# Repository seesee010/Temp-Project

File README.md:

# Custom PCB

> [!IMPORTANT]
> You will only find the kicad here, as everything else is not finished,yet!

This is my project, fully made with KiCad.
The purpose is that it will show temp and hum on display (spi).

## Preview
View PDF: [PDF-Workflow](./docs/pdf/Temp-Project.pdf)

View Website: [Website](https://seesee010.github.io/Temp-Project/)

View PCB:

## License
GPL 2.0 - see License file for more Information.

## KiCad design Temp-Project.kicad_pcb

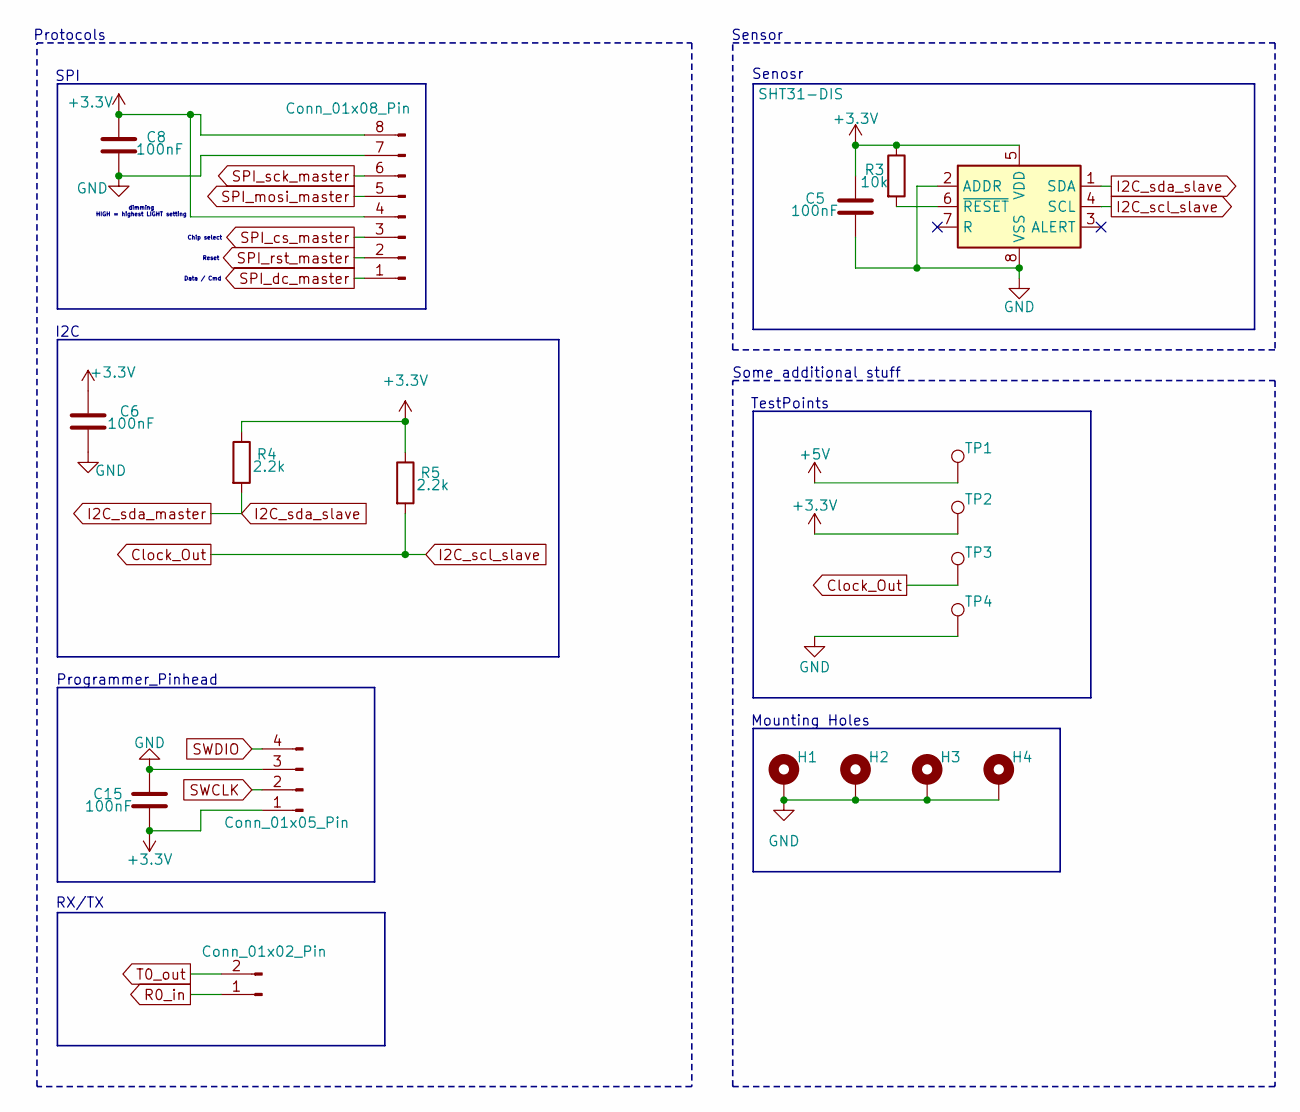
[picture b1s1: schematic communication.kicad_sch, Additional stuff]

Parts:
C5, C6, C8, C15: 100nF; C_0603_1608Metric
H1, H2, H3, H4: MountingHole_Pad; MountingHole_2.2mm_M2_DIN965_Pad
J2: Conn_01x05_Pin; PinHeader_1x05_P2.54mm_Vertical
J3: Conn_01x02_Pin; PinHeader_1x02_P2.54mm_Vertical
J4: Conn_01x08_Pin; PinHeader_1x08_P2.54mm_Vertical
R3: 10k; R_0402_1005Metric
R4, R5: 2.2k; R_0402_1005Metric
TP1, TP2, TP3, TP4: TestPoint; TestPoint_Pad_1.0x1.0mm
U3: SHT31-DIS; Texas_S-PWSON-N6-HDC2080

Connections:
+3.3V: C5.1, C6.1, C8.1, C15.2, J2.1, J4.4, J4.8, R3.1, R4.1, R5.1, TP2.1, U3.5 (VDD); also elsewhere on the board
+5V: TP1.1; also elsewhere on the board
Clock_Out: R5.2, TP3.1, U3.4 (SCL); also elsewhere on the board
GND: C5.2, C6.2, C8.2, C15.1, H1.1, H2.1, H3.1, H4.1, J2.3, J4.7, TP4.1, U3.2 (ADDR), U3.8 (VSS), U3.9 (VSS); also elsewhere on the board
I2C_sda_master: R4.2, U3.1 (SDA); also elsewhere on the board
unnamed: R3.2, U3.6 (~RESET)
R0_in: J3.1; also elsewhere on the board
SPI_cs_master: J4.3; also elsewhere on the board
SPI_dc_master: J4.1; also elsewhere on the board
SPI_mosi_master: J4.5; also elsewhere on the board
SPI_rst_master: J4.2; also elsewhere on the board
SPI_sck_master: J4.6; also elsewhere on the board
SWCLK: J2.2; also elsewhere on the board
SWDIO: J2.4; also elsewhere on the board
T0_out: J3.2; also elsewhere on the board

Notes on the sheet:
TestPoints
Programmer_Pinhead
Senosr
SPI
Reset
Some additional stuff
dimming HIGH = highest LIGHT setting
Mounting Holes
RX/TX
I2C
Data / Cmd
Protocols
Sensor
Chip select

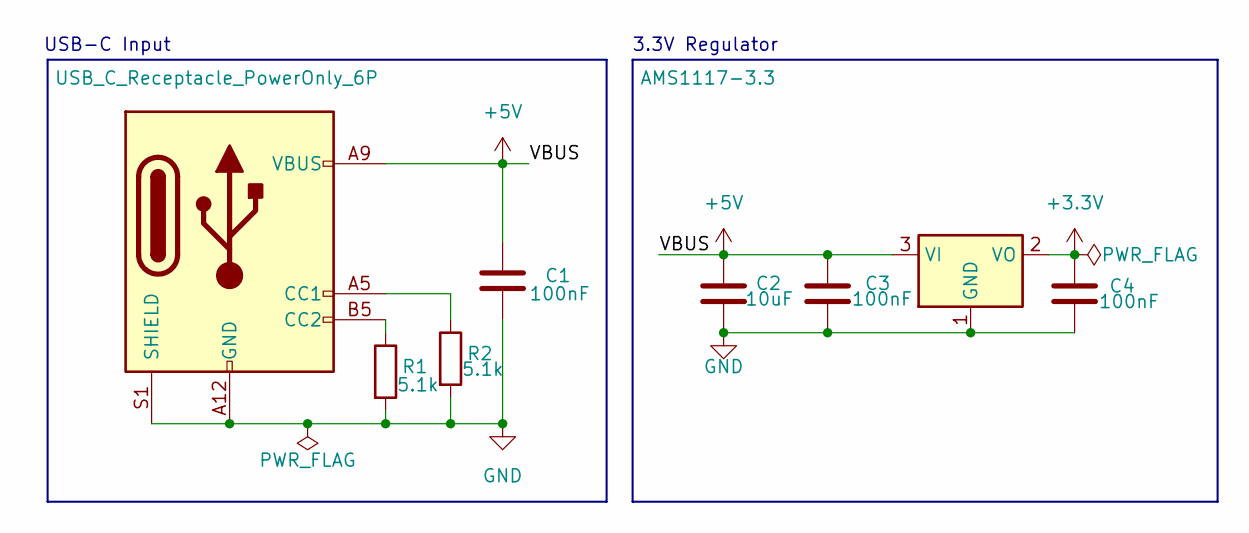
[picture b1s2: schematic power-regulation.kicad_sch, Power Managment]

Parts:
C1, C3, C4: 100nF; C_0603_1608Metric
C2: 10uF; C_0603_1608Metric
J1: USB_C_Receptacle_PowerOnly_6P; USB_C_Receptacle_GCT_USB4135-GF-A_6P_TopMnt_Horizontal
R1, R2: 5.1k; R_0402_1005Metric
U1: AMS1117-3.3; SOT-223-3_TabPin2

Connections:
+3.3V: C4.1, U1.2 (VO); also elsewhere on the board
+5V: C1.2, C2.1, C3.1, J1.A9 (VBUS), J1.B9 (VBUS), U1.3 (VI); also elsewhere on the board
GND: C1.1, C2.2, C3.2, C4.2, J1.A12 (GND), J1.B12 (GND), J1.S1 (SHIELD), R1.2, R2.2, U1.1 (GND); also elsewhere on the board
unnamed: J1.A5 (CC1), R2.1
unnamed: J1.B5 (CC2), R1.1

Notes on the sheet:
USB-C Input
3.3V Regulator

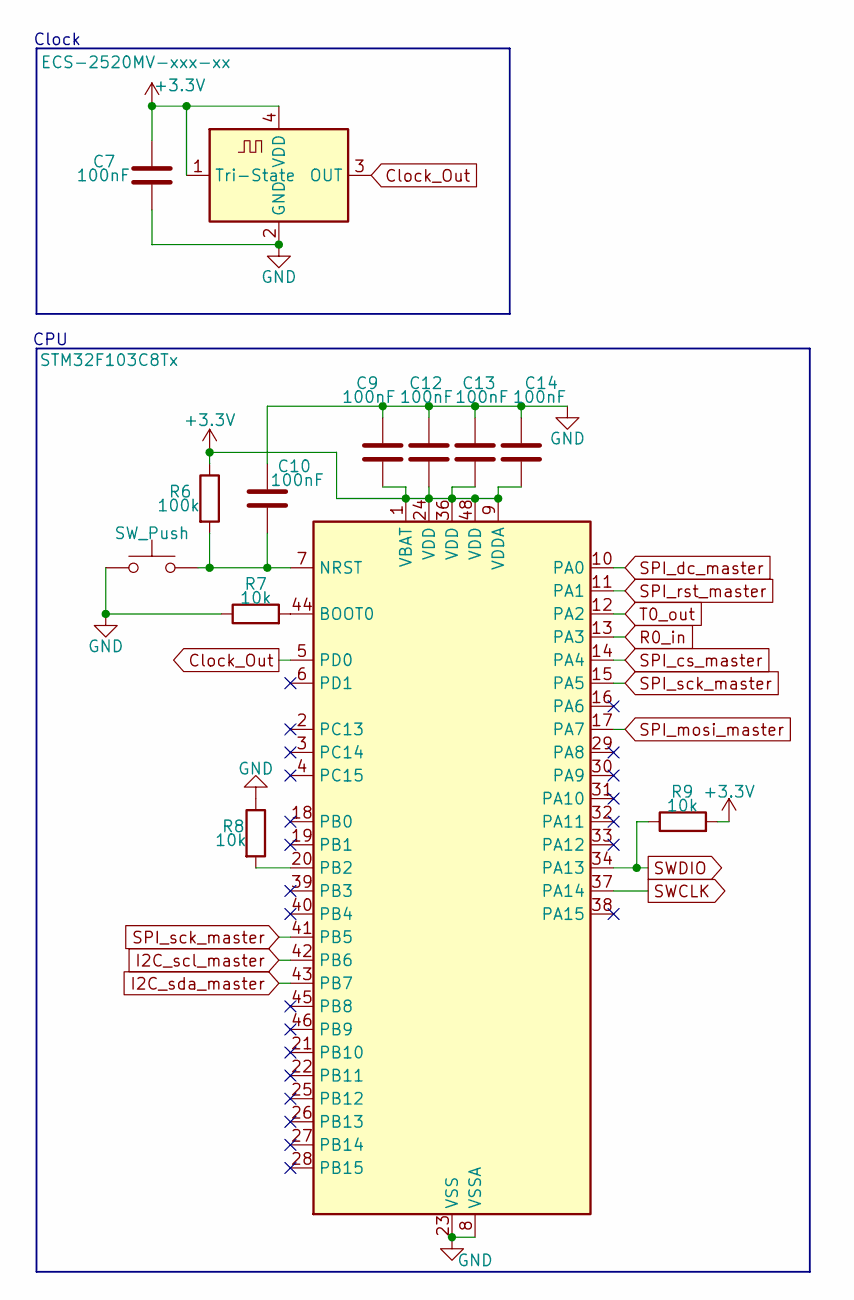
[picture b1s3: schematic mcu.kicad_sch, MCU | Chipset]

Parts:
C7, C9, C10, C12, C13, C14: 100nF; C_0603_1608Metric
R6: 100k; R_0402_1005Metric
R7, R8, R9: 10k; R_0402_1005Metric
SW1: SW_Push; SW_Push_1P1T_NO_CK_KMR2
U2: STM32F103C8Tx; LQFP-48_7x7mm_P0.5mm
Y1: ECS-2520MV-xxx-xx; Oscillator_SMD_EuroQuartz_XO53-4Pin_5.0x3.2mm

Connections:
+3.3V: C7.1, C9.2, C12.2, C13.2, C14.2, R6.1, R9.2, U2.1 (VBAT), U2.9 (VDDA), U2.24 (VDD), U2.36 (VDD), U2.48 (VDD), Y1.1 (Tri-State), Y1.4 (VDD); also elsewhere on the board
Clock_Out: U2.5 (PD0), Y1.3 (OUT); also elsewhere on the board
GND: C7.2, C9.1, C10.1, C12.1, C13.1, C14.1, R7.1, R8.1, SW1.1, U2.8 (VSSA), U2.23 (VSS), U2.35 (VSS), U2.47 (VSS), Y1.2 (GND); also elsewhere on the board
I2C_scl_master: U2.42 (PB6)
I2C_sda_master: U2.43 (PB7); also elsewhere on the board
unnamed: R7.2, U2.44 (BOOT0)
unnamed: C10.2, R6.2, SW1.2, U2.7 (NRST)
unnamed: R8.2, U2.20 (PB2)
R0_in: U2.13 (PA3); also elsewhere on the board
SPI_cs_master: U2.14 (PA4); also elsewhere on the board
SPI_dc_master: U2.10 (PA0); also elsewhere on the board
SPI_mosi_master: U2.17 (PA7); also elsewhere on the board
SPI_rst_master: U2.11 (PA1); also elsewhere on the board
SPI_sck_master: U2.15 (PA5), U2.41 (PB5); also elsewhere on the board
SWCLK: U2.37 (PA14); also elsewhere on the board
SWDIO: R9.1, U2.34 (PA13); also elsewhere on the board
T0_out: U2.12 (PA2); also elsewhere on the board

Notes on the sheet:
CPU
Clock

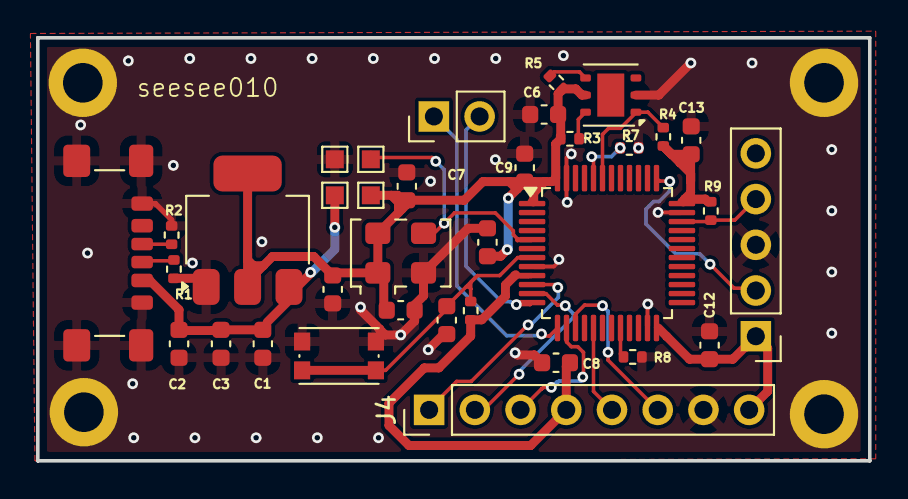
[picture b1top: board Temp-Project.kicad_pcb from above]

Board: 2 copper layers, 46.2 x 23.5 mm, 38 parts (0 on the bottom side), 20 nets.

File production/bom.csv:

Designator,Footprint,Quantity,Value,LCSC Part #
,,1,,
"C1, C10, C12, C13, C14, C3, C4, C5, C6, C7, C8, C9",0603,12,100nF,
C2,0603,1,10uF,
J1,USB_C_Receptacle_GCT_USB4135-GF-A_6P_TopMnt_Horizontal,1,USB_C_Receptacle_PowerOnly_6P,
J2,PinHeader_1x05_P2.54mm_Vertical,1,Conn_01x05_Pin,
J3,PinHeader_1x02_P2.54mm_Vertical,1,Conn_01x02_Pin,
J4,PinHeader_1x08_P2.54mm_Vertical,1,Conn_01x08_Pin,
"R1, R2",0402,2,5.1k,
"R3, R7, R8, R9",0402,4,10k,
"R4, R5",0402,2,2.2k,
R6,0402,1,100k,
SW1,SW_Push_1P1T_NO_CK_KMR2,1,SW_Push,
"TP1, TP2, TP3, TP4",TestPoint_Pad_1.0x1.0mm,4,TestPoint,
U1,SOT-223-3_TabPin2,1,AMS1117-3.3,
U2,LQFP-48_7x7mm_P0.5mm,1,STM32F103C8Tx,
U3,Texas_S-PWSON-N6-HDC2080,1,SHT31-DIS,
Y1,Oscillator_SMD_EuroQuartz_XO53-4Pin_5.0x3.2mm,1,ECS-2520MV-xxx-xx,

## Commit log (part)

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2026-02-22 1. | 2026-23-2
2026-02-22 Add(README.md): Added a new file
2026-02-22 important change
2026-02-23 2. | 2026-02-23 | Mo
2026-02-25 adding
2026-02-25 2026-02-25 | Mi
2026-02-26 2026-02-26 | Do
2026-02-28 2026-02-28
2026-02-28 2026-03-01 | 1
2026-03-01 2026-03-01 | 2
2026-03-01 added a pcb as png
2026-03-01 change the pic to a newer version
2026-03-01 add pic in readme
2026-03-01 add pic in readme | fixed a spelling mistake
2026-03-01 readme had some errors for showing that pic
2026-03-09 2026-03-09 | So-Mo
2026-03-09 Update PCB image path in README
2026-03-09 Rename image.png to PCB.png
2026-03-09 some chore | doc
2026-03-11 2026-03-11
2026-03-11 some bug fixes from 11
2026-03-15 2026-03-16
2026-03-15 small fix
2026-03-15 Update README with project website and PCB link
    Added links to the project website and PCB image.
2026-03-15 Rename ibom.html to index.html
2026-03-15 important
2026-03-15 Add website link to README
2026-03-15 Fix duplicate website link in README
    Removed duplicate website link from README.
2026-03-15 Update PDF link text in README
2026-03-15 Update README with PDF link and license details
    Added PDF link and license information to README.
2026-03-15 Add website preview image to README
    Updated README to include a preview image for the website.

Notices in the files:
schematics/communication.kicad_sch:
GPL-2.0 or newer
